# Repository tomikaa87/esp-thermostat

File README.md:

# esp-thermostat
Smart WiFi thermostat based on the well-known ESP8266 SoC.

Documentation and detailed description will come in the near future...

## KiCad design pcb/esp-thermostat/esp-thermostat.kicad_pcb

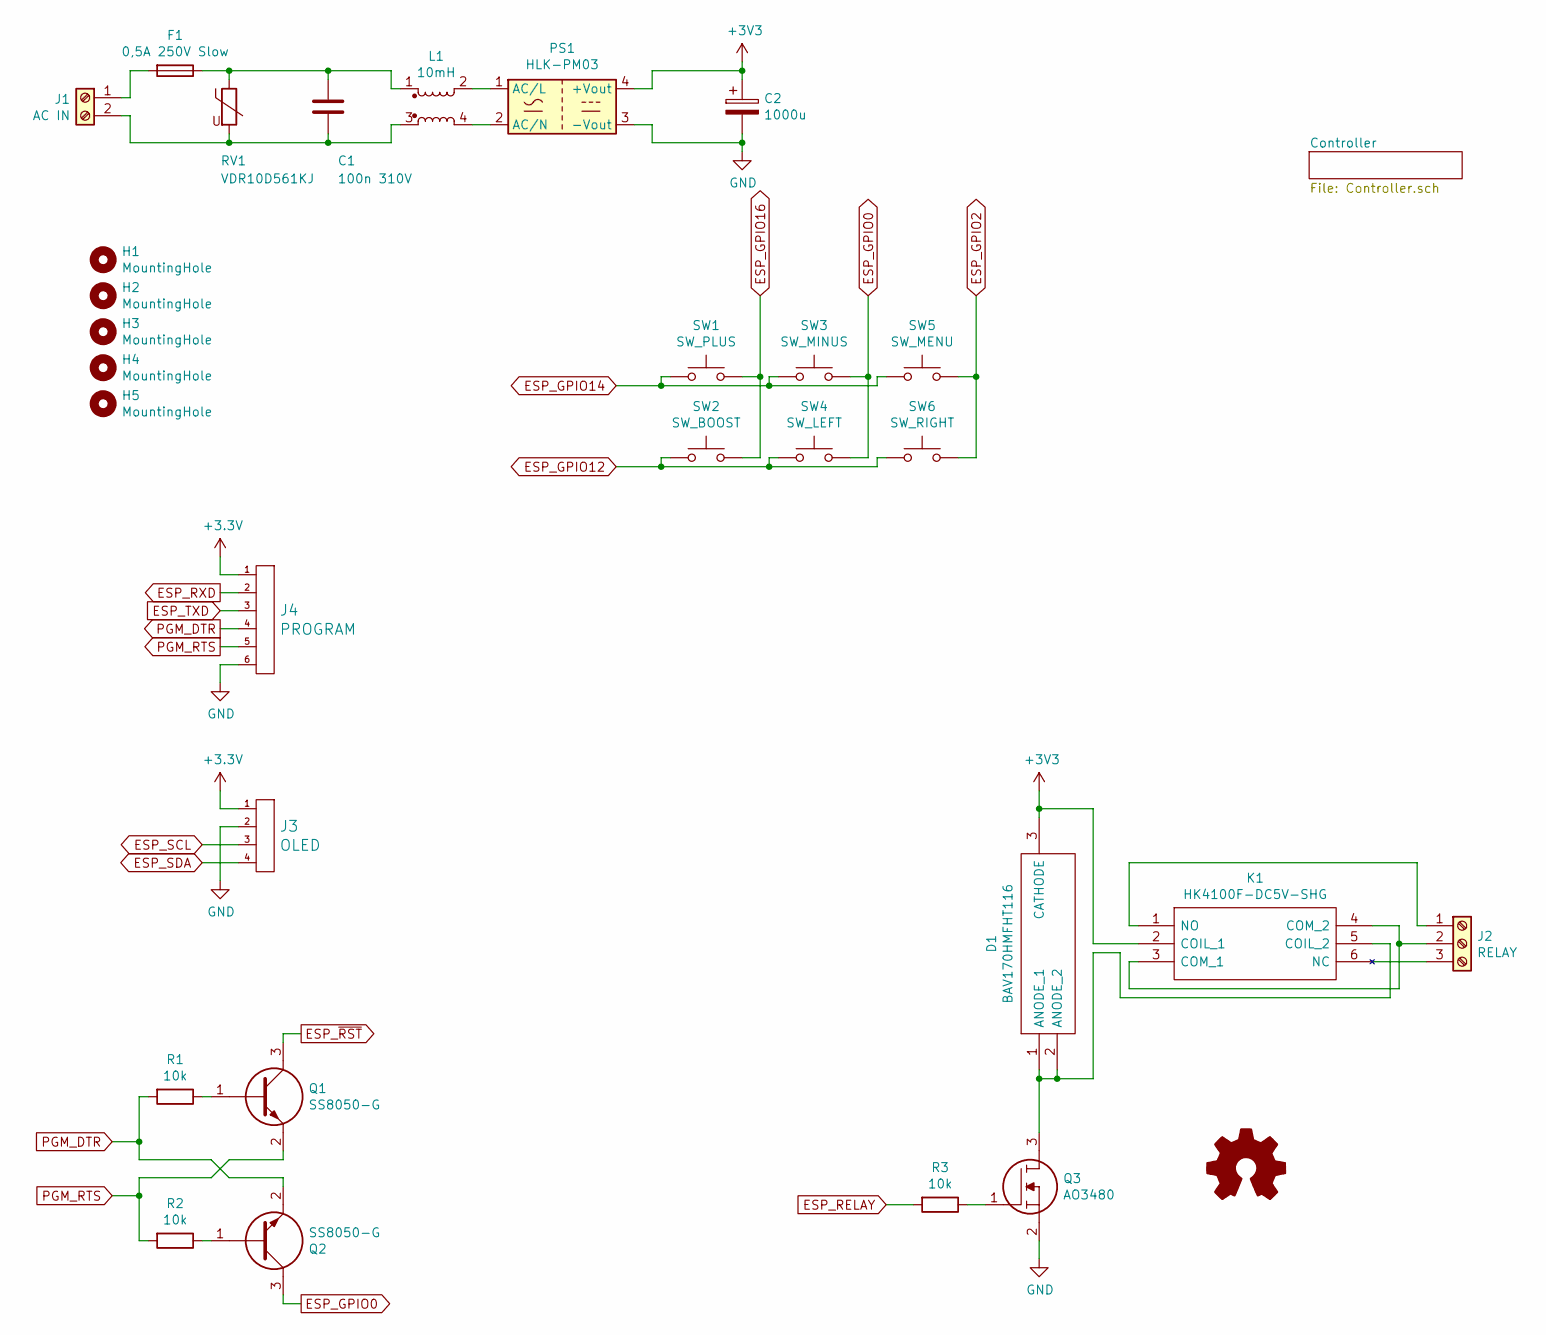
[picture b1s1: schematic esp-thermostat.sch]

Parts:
C1: 100n 310V; R46KI310040M1K
C2: 1000u; CP_Radial_D10.0mm_P5.00mm
D1: BAV170HMFHT116; SOT95P240X115-3N; Manufacturer_Part_Number BAV170HMFHT116; Mouser Part Number 755-BAV170HMFHT116
F1: 0,5A 250V Slow; FUSC10134X305N
H1, H2, H3, H4, H5: MountingHole; MountingHole_2.2mm_M2_ISO14580_Pad
J1: AC IN; mkds_1,5-2
J2: RELAY; mkds_1,5-3
J3: OLED; PinHeader_1x04_P2.54mm_Vertical
J4: PROGRAM; PinHeader_1x06_P2.54mm_Vertical
K1: HK4100F-DC5V-SHG; HK4100FDC5VSHG; Manufacturer_Part_Number HK4100F-DC5V-SHG
L1: 10mH; UU9810MH
PS1: HLK-PM03; Converter_ACDC_HiLink_HLK-PMxx
Q1, Q2: SS8050-G; SOT95P240X115-3N; Manufacturer_Part_Number SS8050-G; Mouser Part Number 750-SS8050-G
Q3: AO3480; SOT95P280X125-3N; Manufacturer_Part_Number AO3480
R1, R2, R3: 10k; R_0805_2012Metric_Pad1.15x1.40mm_HandSolder
RV1: VDR10D561KJ; RV_Disc_D12mm_W6.7mm_P7.5mm
SW1: SW_PLUS; SW_Push_1P1T_NO_6x6mm_FSM2JSMA
SW2: SW_BOOST; SW_Push_1P1T_NO_6x6mm_FSM2JSMA
SW3: SW_MINUS; SW_Push_1P1T_NO_6x6mm_FSM2JSMA
SW4: SW_LEFT; SW_Push_1P1T_NO_6x6mm_FSM2JSMA
SW5: SW_MENU; SW_Push_1P1T_NO_6x6mm_FSM2JSMA
SW6: SW_RIGHT; SW_Push_1P1T_NO_6x6mm_FSM2JSMA

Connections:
ESP_GPIO0: Q2.3, SW3.2, SW4.2; also elsewhere on the board
ESP_GPIO2: SW5.2, SW6.2; also elsewhere on the board
ESP_GPIO12: SW2.1, SW4.1, SW6.1; also elsewhere on the board
ESP_GPIO14: SW1.1, SW3.1, SW5.1; also elsewhere on the board
ESP_GPIO16: SW1.2, SW2.2; also elsewhere on the board
ESP_RELAY: R3.2; also elsewhere on the board
ESP_RXD: J4.2; also elsewhere on the board
ESP_SCL: J3.3; also elsewhere on the board
ESP_SDA: J3.4; also elsewhere on the board
ESP_TXD: J4.3; also elsewhere on the board
ESP_~RST~: Q1.3; also elsewhere on the board
GND: C2.2, J3.2, J4.6, PS1.3 (-Vout), Q3.2; also elsewhere on the board
unnamed: C1.1, F1.1, L1.1, RV1.1
unnamed: C1.2, J1.2, L1.3, RV1.2
unnamed: D1.1 (ANODE_1), D1.2 (ANODE_2), K1.5 (COIL_2), Q3.3
unnamed: F1.2, J1.1
unnamed: J2.1, K1.1 (NO)
unnamed: J2.2, K1.3 (COM_1), K1.4 (COM_2)
unnamed: J2.3, K1.6 (NC)
unnamed: L1.2, PS1.1 (AC/L)
unnamed: L1.4, PS1.2 (AC/N)
unnamed: Q1.1, R1.1
unnamed: Q2.1, R2.1
unnamed: Q3.1, R3.1
PGM_DTR: J4.4, Q2.2, R1.2
PGM_RTS: J4.5, Q1.2, R2.2

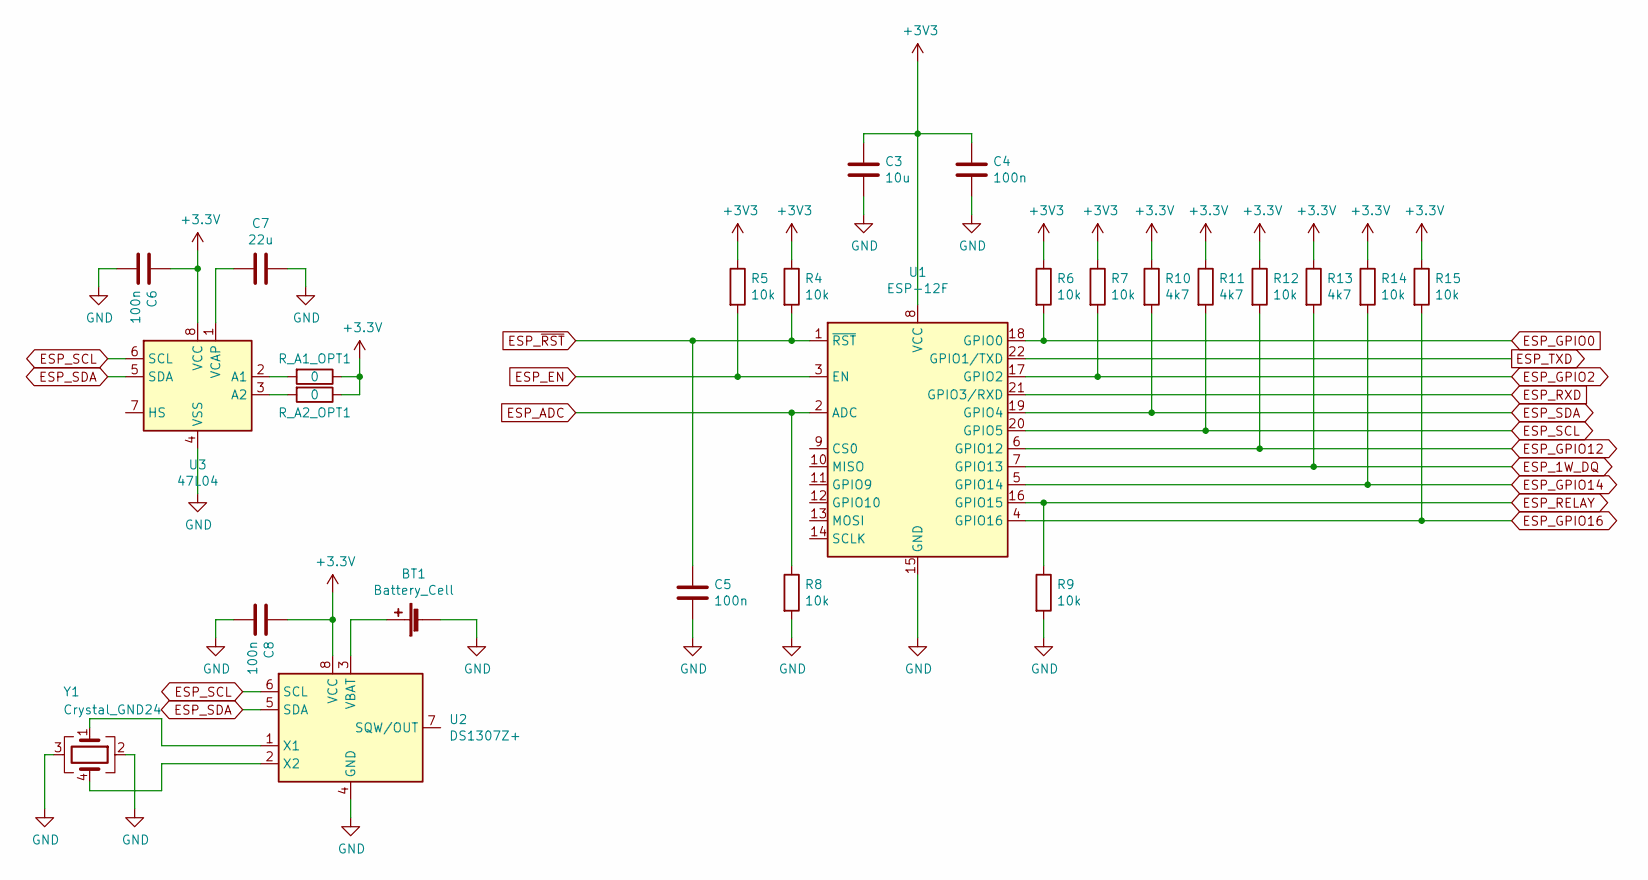
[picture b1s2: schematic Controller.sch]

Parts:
BT1: Battery_Cell; BatteryHolder_CR1632_SMD
C3: 10u; C_0805_2012Metric_Pad1.15x1.40mm_HandSolder
C4, C5, C6, C8: 100n; C_0805_2012Metric_Pad1.15x1.40mm_HandSolder
C7: 22u; C_0805_2012Metric_Pad1.15x1.40mm_HandSolder
R4, R5, R6, R7, R8, R9, R12, R14, R15: 10k; R_0805_2012Metric_Pad1.15x1.40mm_HandSolder
R10, R11, R13: 4k7; R_0805_2012Metric_Pad1.15x1.40mm_HandSolder
R_A1_OPT1, R_A2_OPT1: 0; R_0805_2012Metric_Pad1.15x1.40mm_HandSolder
U1: ESP-12F; ESP-12E_SMD
U2: DS1307Z+; SOIC-8_3.9x4.9mm_P1.27mm
U3: 47L04; SOIC-8_3.9x4.9mm_P1.27mm
Y1: Crystal_GND24; Crystal_SMD_SeikoEpson_MC306-4Pin_8.0x3.2mm

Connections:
ESP_1W_DQ: R13.2, U1.7 (GPIO13); also elsewhere on the board
ESP_ADC: R8.1, U1.2 (ADC)
ESP_EN: R5.2, U1.3 (EN)
ESP_GPIO0: R6.2, U1.18 (GPIO0); also elsewhere on the board
ESP_GPIO2: R7.2, U1.17 (GPIO2); also elsewhere on the board
ESP_GPIO12: R12.2, U1.6 (GPIO12); also elsewhere on the board
ESP_GPIO14: R14.2, U1.5 (GPIO14); also elsewhere on the board
ESP_GPIO16: R15.2, U1.4 (GPIO16); also elsewhere on the board
ESP_RELAY: R9.1, U1.16 (GPIO15); also elsewhere on the board
ESP_RXD: U1.21 (GPIO3/RXD); also elsewhere on the board
ESP_SCL: R11.2, U1.20 (GPIO5), U2.6 (SCL), U3.6 (SCL); also elsewhere on the board
ESP_SDA: R10.2, U1.19 (GPIO4), U2.5 (SDA), U3.5 (SDA); also elsewhere on the board
ESP_TXD: U1.22 (GPIO1/TXD); also elsewhere on the board
ESP_~RST~: C5.1, R4.2, U1.1 (~RST); also elsewhere on the board
GND: BT1.2 (-), C3.2, C4.2, C5.2, C6.2, C7.1, C8.2, R8.2, R9.2, U1.15 (GND), U2.4 (GND), U3.4 (VSS), Y1.2, Y1.3; also elsewhere on the board
unnamed: BT1.1 (+), U2.3 (VBAT)
unnamed: C7.2, U3.1 (VCAP)
unnamed: R_A1_OPT1.2, U3.2 (A1)
unnamed: R_A2_OPT1.2, U3.3 (A2)
unnamed: U2.1 (X1), Y1.1
unnamed: U2.2 (X2), Y1.4

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
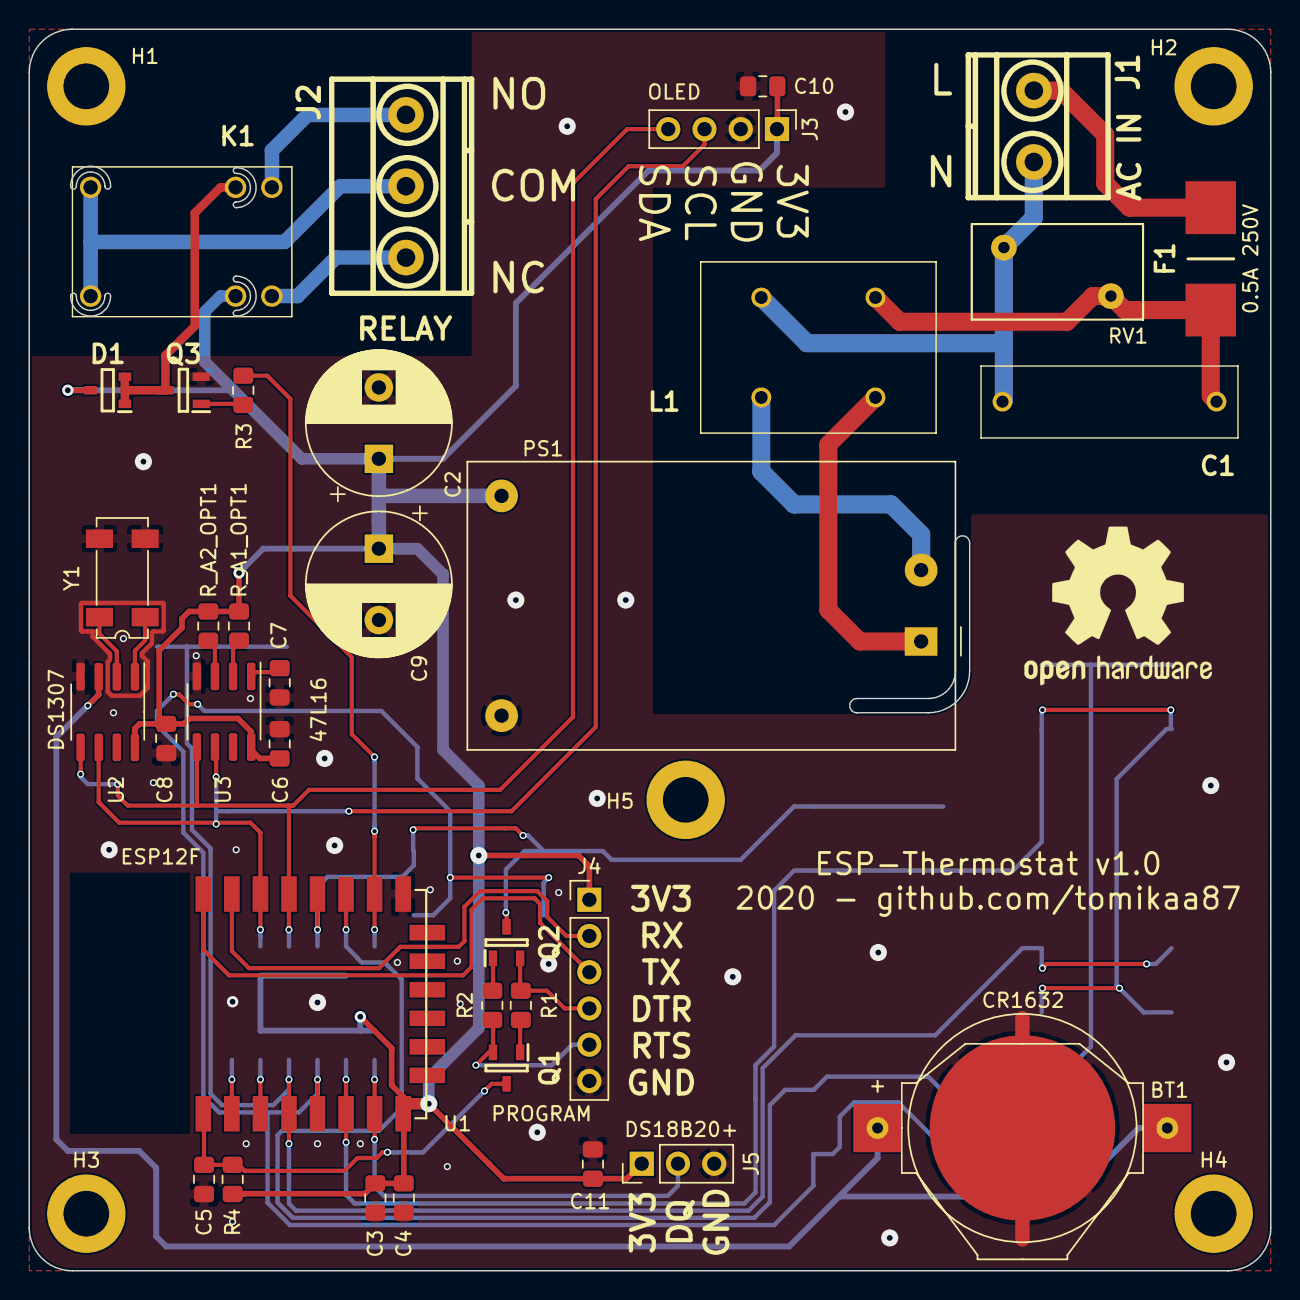
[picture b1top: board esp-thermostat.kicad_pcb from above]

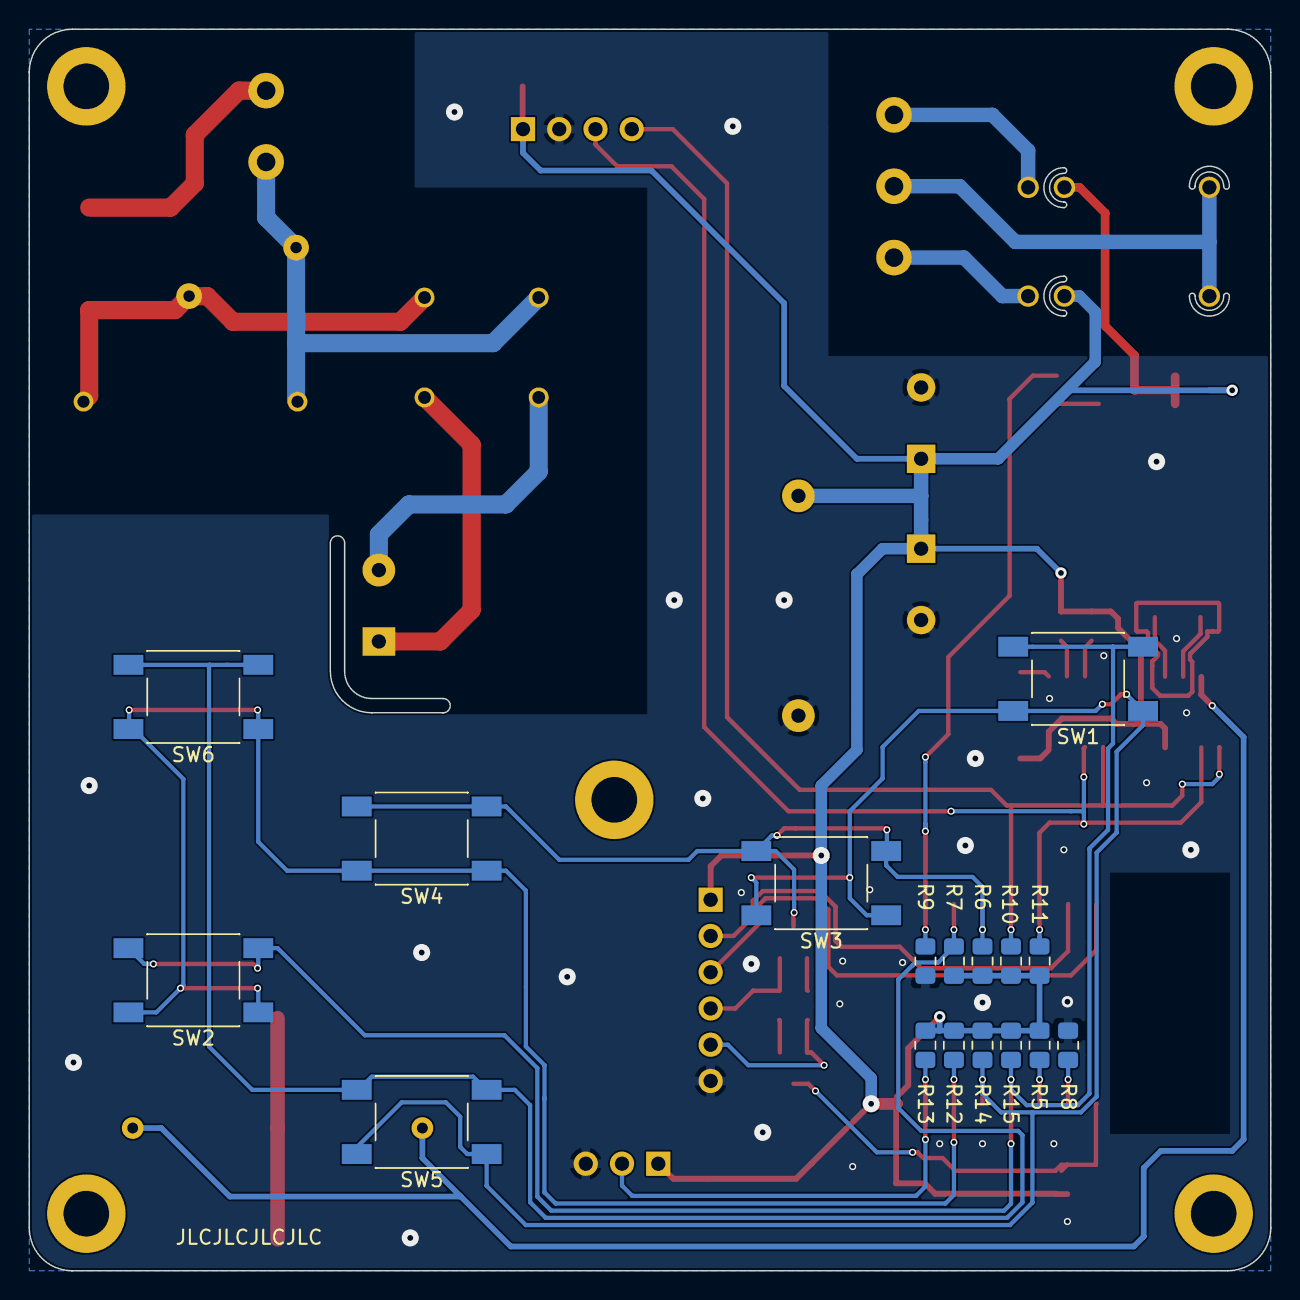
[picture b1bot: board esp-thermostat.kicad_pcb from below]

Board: 2 copper layers, 87.0 x 87.0 mm, 59 parts (17 on the bottom side), 36 nets.

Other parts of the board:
C9: 1000u; CP_Radial_D10.0mm_P5.00mm
C10, C11: 100n; C_0805_2012Metric_Pad1.15x1.40mm_HandSolder
J5: DS18B20+; PinHeader_1x03_P2.54mm_Vertical
LOGO1: Logo_Open_Hardware_Small; OSHW-Logo2_14.6x12mm_SilkScreen

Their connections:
ESP_1W_DQ: J5.2; also elsewhere on the board
GND: C9.2, C10.2, C11.2, J5.3; also elsewhere on the board

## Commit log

2019-11-30 Housing: add buttons
2019-11-30 Housing: add OLED dummy model
2019-11-30 Housing: add backplate
2019-11-30 Housing: begin resizing to 100x100
2019-12-01 Housing: finish resizing, buttons still missing
2019-12-01 Housing: resize buttons
2019-12-01 Housing: shrink button texts
2019-12-08 Route PCB for 100x100 housing
2019-12-22 Small improvements on the PCB
2019-12-22 Add datasheet for SH1106
2019-12-28 PCB: add temp sensor header, optimize routing
2019-12-28 Housing: add PCB model, add top vent holes and dust shield
2020-01-04 PCB: prepare for manufacturing
2020-01-07 Implement WiFi password input in the menu
2020-01-08 Finalize PCB, ready for manufacturing
2020-01-08 Add more documentation
2020-01-08 Finalize the housing
2020-01-08 Housing: add Mefisto 0.4 mesh
2020-01-21 Initial commit of WiFi AP scanning
2020-01-22 Initial commit of new display drivers
2020-01-24 Implement new SSD1306 driver
2020-01-25 Implement text drawing functions in c++
2020-02-23 Add more datasheets
2020-02-23 Adjust housing sizes
2020-02-23 Update keypad mapping to match the layout on the design
2020-02-23 Add new c++-based drivers
2020-02-23 Add missing license headers
2020-02-23 Fix EERAM driver
2020-02-24 Initial commit of MCP7940N RTC driver
2020-02-25 MCP7940N: implement more interface functions
2020-02-27 Integrate new RTC driver
2020-02-28 Stabilize temperature readings
2020-02-28 Convert legacy source to c++
2020-03-07 Modernize keypad driver implementation
2020-03-07 Convert indentation to spaces
2020-03-07 Remove remains of old keypad driver
2020-03-07 Modernize base UI controller class
2020-03-07 Use new display drivers everywhere
2020-04-13 Big refactor step 1
2020-04-13 Big refactor step 2
2020-04-13 Big refactor step 3
2020-04-13 Big refactor step 4
2020-04-13 Big refactor step 5
2020-04-13 Big refactor step 6
2020-04-13 Implement OTA self update
2020-04-13 Improve screen handling
2020-04-13 Refactor Settings
2020-04-13 Improve Settings, implement more efficient I2C driver, fix minor issues
2020-04-13 Do some housekeeping
2020-08-18 (FIXME) improve storing of set temperature
2020-08-18 Migrate to esp-iot-base
2020-08-18 Fix minor findings
2020-10-05 Update esp-iot-base (fix epoch timer ISR crash)
2020-10-05 Critical fix: call CoreApplication::task
2020-10-05 Implement temperature offset handling
2020-10-05 Fix temperature handling in Blynk
2020-10-06 Adjust magnitude of temperature offset
2020-10-06 Update esp-iot-base
2020-10-06 Add PrivateConfig sample
2020-10-06 Remove unused legacy code
2020-10-06 Fix file name capitalization
2020-10-06 Migrate Settings to use esp-iot-base
2020-10-06 Improve settings handling, add more logging
2020-10-06 Remove unused includes
2020-10-06 Fix settings saving and loading
2020-10-13 Add Blynk over SSL support
2020-10-13 Temporarily disable WiFi screen, bump version
2020-10-13 Add license info to TemperatureSensor
2020-10-13 Fix compilation without Blynk over SSL
2020-10-13 Add more logs
2020-10-13 Fix value roll-over in settings menu
2020-10-13 Fix display of next state in Blynk
2020-10-25 Implement debug-mode virtual keypad
2020-10-25 Attempt to fix zero degrees issue with enabled Blynk-over-SSL
2020-12-15 Update esp-iot-base (Blynk freeze fix)
2020-12-15 Bump version
2020-12-21 Update Blynk to 0.6.7 with BearSSL
2020-12-21 Improve WiFi connection stability
2020-12-21 Enforce STA-only WiFi mode
2020-12-21 Fix deactivation of Boost
2020-12-31 Change device to ESP12E with proper settings
2020-12-31 Update esp-iot-base (WiFi Watchdog)
2020-12-31 Add Reboot option to the menu
2020-12-31 Fix wording of reboot screen
2021-01-04 Clamp temperature sensor reading
2021-01-04 Update esp-iot-base (C-Lib clock sync)
2021-01-04 Re-enable Blynk SSL by default
2021-01-04 Update esp-iot-base (Arduino OTA password hash)
2021-01-04 Add upload auth flag to platformio.ini
2021-01-04 Add ArduinoOtaPasswordHash to PrivateConfig.h.sample
2021-01-04 Update esp-iot-base (include base platformio.ini)
2021-05-31 Add host name configuration option; read OTA auth password from env
2021-07-11 Update current temperature continuously
2021-07-20 Make more optimized builds
2021-08-18 Update esp-iot-base; pin platform dependency
2021-08-18 Fix warnings
2021-08-18 Update platformio.ini for v3
2021-08-18 Put large objects into the program space
2021-08-18 Fix some warnings
2021-08-18 Allocate Thermostat statically
2021-08-18 Fix more warnings
2021-08-22 Remove debug code
2021-08-23 Disable WifiScreen and TextInput
2021-08-23 Put log messages into the flash
2021-08-23 Add more build flags
2021-08-31 Add MQTT support
2021-08-31 Report values through MQTT
2021-08-31 Working MQTT commands
2021-08-31 Add missing Utils to esp-iot-base
2021-09-05 Re-subscribe to MQTT topics on every reconnect
2022-02-23 Make MQTT switchable from config
2022-02-23 Avoid setting up MQTT if disabled
2022-02-23 Add setting to disable Blynk run-time
2022-03-05 Fix boost active status on MQTT after remote activation
2022-03-05 Add missing compiler definitions
2022-07-04 MQTT: add support for user/pass authentication
2022-08-05 Add new Blynk library
2022-08-05 Integrate with new Blynk
2022-08-06 Disable Blynk, update espressif8266 to 4.0.1
2022-08-06 Fix boost remaining time display
2022-08-06 Fix potential buffer overflows
2022-08-06 Support Home Assistant automatic MQTT discovery
2022-08-06 Optimize memory usage of HA MQTT configs
2022-08-07 Disable periodic HTTP update check by default
2022-11-02 Free up some RAM, disable HTTP OTA update
2022-11-15 Fix possible out-of-bounds writes
2022-12-01 Disable SSL in Blynk
2023-10-30 Implement furnace controller mode
2023-11-03 Add active temperature and heating state entity
2023-11-04 Initial commit of HeatingZoneController
2023-11-04 Add HeatingZoneController tests
2023-11-05 Implement Boost in HeatingZoneController
2023-11-05 Implement basic control in HeatingZoneController
2023-11-05 Organize HeatingZoneController tests
2023-11-05 Add mode transition tests to HeatingZoneController
2023-11-05 Add Boost transition tests to HeatingZoneController
2023-11-06 Implement scheduler in HeatingZoneController
2023-11-07 Start implementing HeatingZone
2023-11-07 Initial commit of HeatingController and FurnaceController
2023-11-07 Implement MQTT integration in HeatingZone
2023-11-08 Update heating state when input parameters change
2023-11-08 Remove old heating controller
2023-11-08 Add updateSchedule()
2023-11-18 Start implementing persistence
2023-11-25 Implement controller state persistence
2023-11-26 Save the default state after failed load
2023-11-26 Fix out-of-bounds write in Setting
2023-11-26 Start implementing a proper MQTT device
2023-11-27 Improve Home Assistant support
2023-11-27 Increase MQTT buffer size
2023-12-22 Implement Energy Optimizer
2024-03-23 Implement window sensor handling
2024-03-23 Fix swapped window state handling
2024-03-23 Use switch config for Remote Window Sensor
2024-03-23 Add heating zone
2024-03-26 Implement open window lock-out
    Avoids calling for heat for the specified time after
    the window sensor indicates a 'Closed' state.
2024-04-06 Create separate devices for individual zones
2024-05-09 Implement heating start delay
2024-06-01 Refactor the UI controller, add test menu
2024-06-02 Menu: implement upward stepping
2024-06-02 Menu: fix overdrawing
2024-06-02 Implement an MVC-like UI architecture
2024-06-15 Modernize resource handling (fonts, assets)
2024-06-16 Modernize large number drawing
2024-06-16 Remove DrawHelper
2024-06-16 Remove Text
2024-06-16 Main screen
2024-09-24 Add various settings screens
2024-09-24 Add more zone settings screens
2024-09-26 Implement new settings with fixed memory layout
2024-09-26 Clean up settings logic in modules
2024-09-26 Re-enable automatic display power saver
2024-09-26 Reduce amount of info logs
2024-09-26 Implement adjustable log level filter
2024-09-26 Change schedule bit order to MSB-first
    To make it more readable on the settings dump,
    MSB-first schedule bit order is used. This way
    the bits can be read sequentiall from left to
    right, so the first half hour segment is bit 7,
    the second segment is bit 6 and so on.
2024-09-26 Implement zone schedule editing
2024-09-27 Add more schedule unit tests
2024-09-27 Implement showing values on a menu item
2024-09-27 Implement display settings screen
2024-09-27 Implement general settings screen
2024-09-27 Implement zone settings screen
2024-09-28 Immediately apply display settings
2024-09-28 Implement remaining zone settings
2024-09-28 Implement log level setting and reboot from main menu
2024-09-28 Re-enable FurnaceController
2024-09-28 Bump version to 1.7.0
2024-09-28 Update data on Main Screen
2024-09-28 Update zone controller clock
2024-09-28 Fix zone mode selection on settings screen
2024-09-28 Show zone status on main screen
2024-09-28 Fix log level setting roll-over
2024-09-28 Disable debug mode zone temperature input
2024-09-28 Remove unused ZoneGeneralSettingsScreen
2024-09-29 Add missing WindowOpen state to zone status
2024-09-29 Add .editorconfig
2024-09-29 Add MQTT packet buffer size requirement
2024-09-29 Use custom fork of PubSubClient
2024-09-29 Add WindowLockout state to zone status
2024-09-29 Set MQTT packet buffer size
2024-09-29 Pre-allocate buffers for log strings
2024-09-29 Implement settings data versioning
2024-09-29 Implement adjustable window lockout duration
2024-09-29 Add documentation for settings versioning
2024-09-29 Revert to original PubSubClient temporaryly
2024-09-29 Bump version to 1.7.1
2024-09-29 Add WiFi and MQTT states to the UI Model
2024-09-30 Add WiFi and MQTT connection status to main screen
2024-09-30 Bump version to 1.7.2
2024-09-30 Show 'Off' state on master disable
2024-09-30 Bump version to 1.7.3
2024-09-30 Use custom PubSubClient (fixed)
2024-09-30 Bump version to 1.7.4
2024-09-30 Create separate deploy environment
2024-09-30 Fix static analysis issues
2024-09-30 Add separate screen for debugging
2024-10-01 Use manual menu capacity for memory efficiency
    Revert back to require setting the capacity
    manually in a template parameter instead of
    a variant with a specified maximum count.
    This saves around 240 Bytes of RAM.
2024-10-01 Bump version to 1.7.5
2024-10-01 Show zone number instead of index in settings
2024-10-01 Bump version to 1.7.6
2024-10-03 Use custom NTP server
2024-10-03 Bump version to 1.7.7
2024-10-04 Remove old UI code
2024-10-04 Remove unused configuration macros
2024-10-06 Fix scrolling of long menus
    In case of menus with more items than the number of displayed items
    (height), stepping down to a point where the menu began scrolling, then
    stepping up and stepping down again, caused the menu to draw the wrong
    items beginning from the current position.
2024-10-06 Add input checks to HeatingZoneController
    To fix a possible oscillation scenario when over/undershoot is 0, add
    limits to hysteresis values. Also clamp the target temperature to avoid
    overheating or letting the room freeze.
2024-10-06 Bump version to 1.7.8
2025-03-31 Use pre-allocated buffers for logging and MQTT generators
2025-04-01 Fix OOM when syslog is enabled
2025-05-07 Avoid calling for heat if master switch is off
2026-02-01 Ignore start delay on temperature override
